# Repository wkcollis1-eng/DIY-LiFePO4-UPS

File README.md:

<div align="center">

# DIY LiFePO₄ UPS for a Home Assistant Host & Xfinity XB7 Modem

**12 V LiFePO₄ DC UPS · 18 V boost rail for the host · ESPHome coulomb-counting monitor · bench top-off charger (commissioning)**

</div>

A 12 V LiFePO₄ DC uninterruptible power supply. It keeps a Home Assistant host (ASRock N100DC-ITX) and an Xfinity XB7 cable modem running through grid outages, shuts the host down cleanly before the battery runs out, and recovers by itself when power returns. A Mean Well DIN-rail supply floats a 10 Ah pack through a MOSFET ideal diode. A Victron BatteryProtect provides the hardware low-voltage disconnect. An 18 V Pololu boost feeds the host. An ESPHome monitor on a purpose-built carrier PCB coulomb-counts every outage into Home Assistant.

The project was built in early 2026 around a Home Assistant Green, which ran directly on the 12 V bus. That host has been retired. The HA host is now the N100DC, which has run from this UPS since 2026-08-29; its 19 V ±10 % input window [S, ASRock N100DC-ITX manual] is why the boost exists. Documents dated before August 2026 describe the HA Green build; [Documentation](#documentation) says which ones are current.

Figures in this README carry the repository's provenance tags: **[M]** measured, **[S]** specification or prior document, **[D]** derived from [M]/[S] by stated arithmetic, **[I]** inferred and not yet tested, with the observation that would falsify it.

> **Honest context:** An $85 APC BE600M1 provides comparable backup for a modem and a small host. The case for building this instead (no inverter stage, sub-millisecond DC switchover by design, LiFePO₄ chemistry, direct Home Assistant telemetry) is in [design-rationale.md](docs/design-rationale.md). That document and its 10-year cost comparison were written for the March 2026 HA Green build and do not include the boost or the monitor PCB. Build this if those tradeoffs matter to you, and read [Current status](#current-status) first.

---

## ⚠️ Safety Warning

> [!CAUTION]
> **This project involves lithium batteries and AC mains voltage.** Improper handling can cause fire, electric shock, or equipment damage.

- ✅ **Disconnect AC power** before any work inside the enclosure
- ✅ Use appropriate **fusing** on battery connections
- ✅ Never charge LiFePO4 below **0°C (32°F)**
- ✅ Keep a **Class B or ABC fire extinguisher** accessible
- ✅ Follow the boost's energization order, OP-1 in [boost-subsystem-design.md](UPS-Monitor/boost-subsystem-design.md): *battery last-off, first-on; host barrel jack last-on, first-off*. This keeps the host off every connect transient.
- ✅ Review [docs/safety.md](docs/safety.md) before building

**Disclaimer:** Information provided for educational purposes only. Build at your own risk.

---

## Current Status

*As of 2026-10-16.*

| Area | State |
| :--- | :--- |
| Service | In service. Carries the XB7, and since 2026-08-29 the N100DC host |
| Protection ladder | Run end-to-end to the hardware LVD for the first time on 2026-09-15, including survival sleep; recovered with no intervention [M] |
| Capacity | **Well below its May 2026 value, by more than the test conditions can explain; cause not yet identified** (below) |
| Unattended recovery | Guaranteed only for outages that reach LVD, until the boost EN shed is fitted (below) |
| Monitor | UPS-Monitor-THT Rev 1 PCB, ESPHome firmware V1.20 (deployed 2026-09-16) |
| Top-off charger | Built and on the bench, design rev 0.17. Firmware V0.5 flashed 2026-10-30; 17 sessions so far, five of them DONE and the last ten on the UPS's own pack, and one BMS cut missed by FW-5 on V0.4, whose fix in V0.5 stays open until T17 (O18). T0–T17 not yet run |

> [!IMPORTANT]
> **Capacity shortfall.** On 2026-09-15 the pack delivered **2.5331 Ah / 31.821 Wh** from onset to LVD [M, firmware coulomb counter; independent HA-side integration agrees to +0.95 %]. Over the same voltage span at the same load, it delivered **42.4 % less charge than on 2026-09-01**, fourteen days earlier [D, [09-15 report](reports/UPS_Report_2026-09-15_Full_Discharge_Survival_Test.md) §4.3, n = 1 run each]. Measured LVD to LVD, it is 39.4 % below the 4.179 Ah of 2026-05-06 [D, same report]. Rate effects, Peukert, float droop and temperature together account for under 10 % of the LVD-to-LVD gap and none of the load-matched gap [D, §4.4].
>
> The leading candidate is cell imbalance or one weak cell [I, §4.5]. The direct falsifier, per-cell voltage at the end of discharge, cannot be measured: the pack is sealed and has no balance taps. Open Items 14a and 16 are the non-invasive substitutes ([Open work](#open-work)).
>
> **Every runtime and capacity figure from before September 2026, including the "~3.6 h / 4.18 Ah" this README used to quote, describes a pack and a load that no longer exist.**

### Unattended-recovery gap

The boost takes its input from the BP-65 load output, and its EN pin is not yet driven. `hassio.host_shutdown` therefore leaves the N100DC in S5 soft-off with 18 V still applied. Its BIOS setting *Restore on AC/Power Loss = Power On* acts only on a power cycle at the jack. **If AC returns after the graceful shutdown but before the pack reaches LVD, the host stays off until someone presses its power button** [D, [08-31 report](reports/UPS_Report_2026-08-31_Boost_Integration.md) §3].

Outages that reach LVD do recover, because the BP-65 collapses the rail. On 2026-09-15 the host booted with no button press after AC was restored [M]. The 09-15 report's Open Item 1 records why one operator-timed restoration does not fully establish the BIOS behaviour.

The fix is designed and not built: an EN shed from the monitor through an N-FET, latched low for the rest of the outage and released only on confirmed AC return. In [BOOST-DS-r1](UPS-Monitor/boost-subsystem-design.md) this is design rule DR-1 and procedure OP-2.

---

## System Overview

```
 120 VAC ─► Mean Well HDR-60-12 ─► MOSFET ideal diode ─┐
            13.3 V float, 54 W / 4.5 A                 │
                                                       ▼
            ┌──────────────────────── 12 V bus (Wago) ──────────────────────┐
            │                                                               │
     INA260 (battery branch, + = charging)                       Victron BP-65 LVD
            │                                               off 11.80 V / on 12.80 V + 30 s
   Cyclenbatt 12 V 10 Ah LiFePO₄                                            │
   (sealed, internal BMS)                                ┌──────────────────┴─────────────────┐
            │                                            ▼                                    ▼
   UPS-Monitor-THT  ◄── TB1 → F1 1 A                Xfinity XB7                    Pololu U3V70A boost
   XIAO ESP32-C3 · D24V7F3 · DS18B20                (12 V direct)                  18.0 V · 5 A-fused lead
            │ Wi-Fi                                                                           ▼
            └──────────────────────────► Home Assistant ◄──────────────────── ASRock N100DC-ITX (HA host)
```

When AC is present, the PSU holds the bus at float and the pack sits at equilibrium. When AC fails, the ideal diode blocks and the pack carries the loads. The monitor is fed upstream of the BP-65, so it stays powered after the LVD trip and can run survival sleep. It measures the battery branch: the INA260 sits between the Wago bus (VIN+) and Battery+ (VIN−), and the metered current runs on 16 AWG through the breakout's own terminals, not through PCB copper [S, `ups-monitor.yaml` header].

---

## Key Specifications

| Parameter | Value | Basis |
| :--- | :--- | :--- |
| PSU | Mean Well HDR-60-12, 54 W / 4.5 A, trimmed to 13.3 V and lacquered | [S, HDR-60 datasheet] |
| Float at the bus, boost era | 13.1970 V mean (13.2325 V before the boost), 23.3 mV above the 13.15 V on-battery threshold; 0 false on-battery events in 26,413 samples | [M, 08-31 report] |
| Battery | Cyclenbatt 12 V 10 Ah LiFePO₄, 4S, sealed: no balance taps, no BMS telemetry | [S, nameplate]; sealed [M, owner] |
| Usable capacity | **2.5331 Ah / 31.821 Wh**, onset to LVD, 2026-09-15. Under investigation | [M] |
| LVD | Victron BP-65: disconnect 11.80 V after its delay, reconnect 12.80 V after 30 s. Trips seen: 11.77 V (2026-03-26); last telemetry before the 2026-09-15 trip 11.675 V | [S, BP-65 manual]; trips [M] |
| Load on battery | 2.089 A / 26.80 W steady, 2.533 A / 32.48 W peak (host + XB7 + monitor) | [M, 2026-08-29 outage, n = 156] |
| Load after host shutdown | ~1.40 A (XB7 + monitor) | [M, 2026-09-15] |
| AC at the outlet | 30.554 W with the boost; 16.832 W before it | [M, 08-31 report] |
| Boost | Pololu U3V70A set to 18.0 V and lacquered; input from the BP-65 load output; EN not yet driven | [S, BOOST-DS-r1] |
| Host input window | 17.1–20.9 V (19 V ±10 %) | [S, ASRock N100DC-ITX manual] |
| Recharge | Limited by the PSU's 4.5 A constant-current limit: peak captured 4.4465 A, a lower bound | [S]; [M, 2026-09-15] |
| Switchover | No interruption seen by the XB7 or the host in the 2026-08-29, 09-01 or 09-15 outages. The <1 ms figure is the ideal diode's design value, not a measurement: 5 s telemetry cannot resolve it | [M]; <1 ms [S] |
| Monitor | UPS-Monitor-THT Rev 1: XIAO ESP32-C3, Adafruit INA260 (socketed), DS18B20, Pololu D24V7F3; ESPHome firmware V1.20 | — |
| Enclosure | LeMotech ABS, 9.6″ × 7.6″ × 4.5″; IP65 as sold, IP4X once vented | [S, [supplemental-analysis.md](docs/supplemental-analysis.md)] |
| Build cost | $223.88 for the March 2026 build; excludes the monitor PCB and the boost subsystem | [S, [bom.md](docs/bom.md)] |

---

## Operating Modes and Protection Ladder

Thresholds are the V1.20 firmware's substitutions [S, [`ups-monitor.yaml`](UPS-Monitor/ups-monitor.yaml)]. The Home Assistant side is the `ups_*_v3` automation chain in [home-assistant-config](https://github.com/wkcollis1-eng/home-assistant-config).

1. **AC present.** The PSU holds the bus at float through the ideal diode, and the pack sits at about 0 A. The 13.3 V ceiling keeps the bus inside what the loads tolerate, at the cost of holding the pack near 65 % SOC [S, 05-06 report §4.3]. That is why the [top-off charger](#planned-top-off-charger) is planned.
2. **AC fails.** The ideal diode blocks and the pack carries the loads with no interruption. `on_battery` sets when the bus falls below 13.15 V.
3. **Discharge phases.** The firmware tracks Settling, then Plateau (≥ 12.65 V), Knee (12.40–12.65 V) and Cliff (≤ 12.40 V). It counts Ah and Wh and estimates the runtime remaining.
4. **Graceful host shutdown.** Home Assistant calls `hassio.host_shutdown` on the first of three triggers, after a 30 s revalidation:
   - `cliff_imminent`: EMA voltage slope below −10 mV/min, with V < 12.65 V and the pack discharging, held 180 s;
   - `voltage_warning`: 12.40 V;
   - a runtime estimate under 8 min.

   The XB7 stays up.
5. **Hard fallback.** `voltage_critical` (12.20 V, held 10 s) calls the host shutdown with no revalidation, in case the graceful path has not completed.
6. **LVD.** The BP-65 opens at 11.80 V after its delay, dropping the XB7 and the boost. The monitor stays powered.
7. **Survival sleep.** When the load collapses at the trip (on battery, −0.30 A < I < +0.20 A), the monitor deep-sleeps in 120 s cycles with at most 60 s awake each, rather than draining the pack awake, and records each wake voltage in flash. It exits when V ≥ 13.0 V.
8. **AC returns.** The PSU recharges at its 4.5 A current limit and the BP-65 reconnects 30 s after the bus passes 12.80 V. The boost restarts, and the host powers on if it lost DC (see the [recovery gap](#unattended-recovery-gap)).

**What the record shows about the ladder:**

- **Graceful shutdown.** It first fired in May 2026, via `cliff_imminent`. In both boost-era runs, every attempt aborted at least once before one held [D, the firmware replayed on both runs' data, 09-15 report §6.1, n = 2; the 09-15 abort was also seen in HA, M]. The slope term's noise is sd 18.7–24.0 mV/min against a −10 mV/min threshold [M]. V1.20 raised the hold from 60 s to 180 s for this reason, and that change has not yet been exercised in an outage.
- **`voltage_critical` fallback.** It has never been the path that shut a running host down [M].
- **Host-down to LVD.** On 2026-09-15 this took 52 min 47 s at ~1.40 A, with the BP-65 as the only protection [M]. That margin was measured on a pack whose capacity is changing, so it does not set a threshold.

---

## Monitor

### Hardware: UPS-Monitor-THT Rev 1

- KiCad 10, 2-layer, 44 × 77 mm, drawn for OSH Park [S, `ups-monitor.yaml` header]. It replaced the SBB400 breadboard build.
- The Adafruit INA260 (#4226) breakout sits in socket U2. The metered current never touches PCB copper. The board's own supply runs from TB1 through F1 (1 A slow-blow) to a Pololu D24V7F3 3.3 V regulator.
- DS18B20 battery probe on TB2. I²C on GPIO6/GPIO7, 1-Wire on GPIO10.
- Files: [`UPS-Monitor-THT.kicad_pcb`](UPS-Monitor/UPS-Monitor-THT.kicad_pcb), Gerbers in [`UPS-Monitor-THT-Rev_1.zip`](UPS-Monitor/UPS-Monitor-THT-Rev_1.zip), and renders in [`UPS-Monitor/`](UPS-Monitor/).
- The U2 footprint also accepts an INA228 breakout. The firmware is INA260-specific, and an INA228 remaps socket pin 5, so do not substitute one without re-validating.

### Firmware: `ups-monitor.yaml` V1.20

[`UPS-Monitor/ups-monitor.yaml`](UPS-Monitor/ups-monitor.yaml) is the deployed build, byte-identical to the file on the HA host. Credentials resolve through `!secret`; no `secrets.yaml` is in this repository. Every revision is recorded in its header changelog.

What the firmware does:
- coulomb-counts Ah and Wh per outage and over the pack's life;
- runs the discharge-phase state machine and the `cliff_imminent` slope detector;
- estimates runtime remaining;
- estimates internal resistance at outage onset;
- keeps survival-sleep records in NVS;
- watches for stale INA260 data.

V1.20 (2026-09-16) changes:
- V, I and P are now published from one paired read. Before, they ran on free-running clocks, with a V-to-I skew re-drawn on every boot (~1.29 s on the 09-15 boot [M, 09-15 report §10.3]);
- a windowed Apparent-Ri gate;
- `cliff_imminent` hold raised from 60 s to 180 s;
- outage duration now stops at AC return;
- hysteresis on the fully-charged detector.

The survival-sleep design is documented in [`UPS_SurvivalSleep_Design_Summary_v12.md`](UPS-Monitor/UPS_SurvivalSleep_Design_Summary_v12.md). That document tracks the firmware through V1.14, and its currency note lists what changed after.

> [!NOTE]
> **Known issue: the `INA260 Alert` entity cannot fire.** The Rev 1 PCB routes the INA260's ALERT (socket pin 5, R2 pull-up) to XIAO D3 = GPIO5. The firmware, and its header pin map, read GPIO3 (D1), which is unconnected [M, KiCad pad positions; owner-confirmed 2026-10-01]. Nothing depends on it: the firmware arms no alert condition and no automation reads the entity. A one-pin fix is written and held until it can be bench-tested.

---

## Test History

| Date | Event | Load | Result | Source |
| :--- | :--- | :--- | :--- | :--- |
| 2026-03-25/26 | Commissioning: two discharges on a substitute load (Netgear R6400) | ~7 W DC | BP-65 tripped at 11.77 V [M, Shelly ADC] | [commissioning.md](docs/commissioning.md) |
| 2026-03-26 → 04-05 | Commissioning window and relocation to the permanent site | HA Green + XB7 | Stable float | [04-05 report](reports/UPS_Report_2026-04-05.md) |
| 2026-05-06 | Outage to LVD; first INA260 coulomb count; first graceful shutdown | HA Green + XB7, 1.18 A / 14.9 W | **4.179 Ah / 53.271 Wh** [M]; ~213 min AC-fail to LVD [D, 10:25:20 → ~13:58:30 UTC] | [05-06 report](reports/UPS_Report_2026-05-06.md) |
| 2026-06-18 | Partial outage; AC restored at 12.452 V, before any cliff | 1.186 A / 15.18 W | 3.62 Ah / 46.34 Wh in 183.3 min [M]; no protection automation fired | [06-18 report](reports/UPS_Report_2026-06-18.md) |
| 2026-08-29 | First outage after the boost was fitted | 2.089 A / 26.80 W | XB7 and host held through switchover [M] | [08-31 report](reports/UPS_Report_2026-08-31_Boost_Integration.md) |
| 2026-09-01 | Deliberate test, stopped at 12.565 V | host + XB7 | 1.833 Ah / 23.369 Wh in 54 min [M] | [08-31 report](reports/UPS_Report_2026-08-31_Boost_Integration.md) |
| 2026-09-15 | **Full discharge to LVD; first survival sleep; recharge** (firmware 1.19) | ~2.05 A, falling to ~1.40 A after the host shut down | **2.5331 Ah / 31.821 Wh** in 1 h 30 m 08 s onset to LVD [M] | [09-15 report](reports/UPS_Report_2026-09-15_Full_Discharge_Survival_Test.md), [data](data/2026-09-15_full_discharge_survival_test/README.md) |

All runs are on the same pack. May and June were on the pre-boost load (~1.18 A); August onward on the N100DC load. None of the pre-September figures predicts the present pack.

### 2026-09-15: what it established

- **Full ladder to the hardware LVD.** The run went Plateau → Knee (09:41:48) → Cliff (10:32:50) → BP-65 trip (10:47:18). The cliff lasted 14 min 28 s [M].
- **Survival sleep, first real exercise.** It ran 5 sleep/wake cycles over a ~12 min 51 s blackout. Wake voltage rose from 11.9275 to 11.9762 V, consistent with an unloaded pack relaxing. It exited cleanly, and the system recovered unattended [M].
- **The recharge is PSU-limited, not pack-limited.** The captured peak, 4.4465 A, is 98.8 % of the HDR-60-12's 4.5 A rating [D, 4.4465 ÷ 4.5]. The bus re-crossed 13.15 V 39 min 25 s after charge current was first seen [D, 11:00:13.67 → 11:39:39]. At the report cutoff, 51 min 49 s in [D, 11:00:13.67 → 11:52:03], 0.792 A was still flowing [M]. A recharge to termination has not been observed (Open Item 16).
- **Data caveats.** The InfluxDB export covers 37.5 of the ~90 discharge minutes, and it holds one stale sample per series written on recorder restart. Read the [reproduction guide](data/2026-09-15_full_discharge_survival_test/README.md) before re-analysing.

### Commissioning, March 2026

The March 25–26 commissioning ran two full discharges on a Netgear R6400 substitute load (~7 W DC), logged by the Shelly Plus Uni at 5 s intervals. The BP-65 tripped at **11.77 V** against its 11.80 V setting [M], and the pack recovered to float on AC return. The Shelly was replaced by the INA260 monitor in April 2026. Its voltage-profile capacity estimate (D3: 4.85 Ah / 62.5 Wh) was superseded by the May coulomb count and should not be used as a baseline.

---

## Open Work

In priority order, from the [09-15 report](reports/UPS_Report_2026-09-15_Full_Discharge_Survival_Test.md) §11 and the [08-31 report](reports/UPS_Report_2026-08-31_Boost_Integration.md) §7:

1. **Open Item 14a: repeat the full discharge at May's current.** Shut the host down before cutting AC, so the load is the XB7 and the monitor only (~1.2–1.4 A). Use the same 11.80 V endpoint and the same instrument as 2026-05-06. This is the decisive capacity test, and it is also the first outage to exercise V1.20's 180 s `cliff_imminent` hold.
2. **Open Item 16: coulomb-count one recharge to termination**, then compare it with the discharge count. This separates real fade from incomplete charge.
3. **Boost EN shed** (DR-1/OP-2) to close the [recovery gap](#unattended-recovery-gap), and the BOOST-DS-r1 §10 scope gate (V1–V5), which is still open.
4. **Build the top-off charger**, then run 14a before and after a top-balance hold.
5. **Fix the INA260 ALERT pin** once it can be bench-tested.

---

## Planned: Top-Off Charger

[`Top-Off-Charger/top-off-charger-design.md`](Top-Off-Charger/top-off-charger-design.md) is the design, rev 0.17, dated 2026-11-02. The board is built, with one rework (its #2814 control pin, design §7.2). §11.1 records the first bench sessions, and §11.2 the first on the UPS's own pack.

The 13.3 V float never takes the cells to balancing voltage. The plan is to take the pack out of the UPS for each session, charge it to full on a Dylannet P20 at 5 A, and then hold it at 14.40 V on a Mean Well HDR-30-15 (worst case ≤ 3.64 A [D, design §4.1]). An ESPHome controller times the hold and logs the current tail.

- **Controller board.** Top Off Charger PCB rev 0.8: KiCad 10, 2-layer, 29.5 × 78 mm, for OSH Park. It carries a XIAO ESP32-C3, an Adafruit INA228 (#5832) with a 15 mΩ shunt, a Pololu #2814 MOSFET switch, a Pololu #5382 ideal diode, a D24V7F3 regulator, a status LED and a Kelvin ground for the INA228. DRC: 0 errors / 34 warnings / 0 unconnected [M]. **Built** (2026-10-28; which file went to fab is not recorded, O11).
- **Protection.** A protection ladder (L1–L8), firmware requirements (FW-1–FW-14) and acceptance tests (T0–T17). The design requires each session to end by itself within its time cap, and nothing to restart a charge after a reboot or an AC blip. Stop, the normal DONE and FW-5 have now worked on the bench, and FW-5 has also missed once (O18); the numbered tests have not run.
- **Firmware.** [`firmware/top-off-charger.yaml`](Top-Off-Charger/firmware/top-off-charger.yaml) V0.5 compiles, was replayed against the five sessions V0.4 ran, and has been flashed since 2026-10-30; it has run two more. T0–T17 have not run (O4, O18).
- **What it cannot do.** It cannot balance a pack whose BMS has no balancer, and nothing documents whether this one has one. The current tail at 14.40 V is the first direct look [I; falsifier: the logged current decays toward zero with no floor]. On 2026-10-29, on a second, new Cyclenbatt pack rather than the UPS's, it fell to 0.16–0.34 mA at 14.30–14.40 V, with no balancer-sized floor [M, design §11.1], and to about 0.13 mA net after 8 h near 14.45 V on 2026-10-30 [D, design §11.1]. The success measure is Open Item 14a before and after. It does not serve Open Item 16, because the P20 does the bulk charge outside its INA228 and has no data port, so its Ah is a hand reading off its display (O10).

---

## Assembly

*Elevation (top) and plan (bottom) views of the LeMotech junction box, interior dimensions in inches. This drawing and the block diagram below predate the boost and the THT monitor PCB.*

---

## Documentation

**Current**

| File | Contents |
| :--- | :--- |
| [reports/UPS_Report_2026-09-15_Full_Discharge_Survival_Test.md](reports/UPS_Report_2026-09-15_Full_Discharge_Survival_Test.md) | Full discharge to LVD, first survival sleep, recharge, capacity shortfall (r3) |
| [data/2026-09-15_full_discharge_survival_test/](data/2026-09-15_full_discharge_survival_test/README.md) | Raw series, logs, capture scripts and reproduction guide for that report |
| [reports/UPS_Report_2026-08-31_Boost_Integration.md](reports/UPS_Report_2026-08-31_Boost_Integration.md) | Boost integration: float and trip-margin effects, outage load, unattended-recovery gap |
| [boost-subsystem-design.md](UPS-Monitor/boost-subsystem-design.md) | BOOST-DS-r1: 18 V boost design, failure analysis, rules DR-1 and OP-1–OP-4, scope gate |
| [UPS-Monitor/ups-monitor.yaml](UPS-Monitor/ups-monitor.yaml) | Monitor firmware V1.20 (header holds the pin map and full changelog) |
| [UPS-Monitor/UPS_SurvivalSleep_Design_Summary_v12.md](UPS-Monitor/UPS_SurvivalSleep_Design_Summary_v12.md) | Survival-sleep engineering basis (tracks firmware through V1.14) |
| [HA Automation/README_HA_UPS_Integration.md](HA%20Automation/README_HA_UPS_Integration.md) | Home Assistant side: the entities, the five `ups_*_v3` automations and their guards, and what the test record shows about them |
| [Top-Off-Charger/top-off-charger-design.md](Top-Off-Charger/top-off-charger-design.md) | Top-off charger design, rev 0.13 (built; commissioning) |
| [CHANGELOG.md](CHANGELOG.md) | Repository changelog |

**Earlier reports** (pre-boost load; figures predate the boost and the September capacity result)

| File | Contents |
| :--- | :--- |
| [reports/UPS_Report_2026-06-18.md](reports/UPS_Report_2026-06-18.md) | Partial outage; decomposition of its charge delta against May |
| [reports/UPS_Report_2026-05-06.md](reports/UPS_Report_2026-05-06.md) | Outage to LVD; first INA260 coulomb count; graceful shutdown confirmed |
| [reports/UPS_Report_2026-04-05.md](reports/UPS_Report_2026-04-05.md) | Inaugural commissioning report |

**Original design set, January–May 2026** (the HA Green build. Figures for load, runtime, cost and lifespan predate the boost and the September capacity result)

| File | Contents |
| :--- | :--- |
| [docs/bom.md](docs/bom.md) | Bill of materials with vendor, price, and notes |
| [docs/wiring.md](docs/wiring.md) | From/to wiring tables, fuse locations, component mounting |
| [docs/specifications.md](docs/specifications.md) | Electrical, performance, and protection spec tables |
| [docs/design-rationale.md](docs/design-rationale.md) | Build-vs-buy analysis, float charging strategy |
| [docs/component-selection.md](docs/component-selection.md) | Per-component selection rationale |
| [docs/cost-analysis.md](docs/cost-analysis.md) | Build cost and 10-year lifecycle comparison |
| [docs/safety.md](docs/safety.md) | AC and battery safety procedures |
| [docs/voltage-drop-analysis.md](docs/voltage-drop-analysis.md) | Wiring resistance and voltage drop |
| [docs/supplemental-analysis.md](docs/supplemental-analysis.md) | Thermal budget, runtime analysis, FMEA |
| [docs/design-specification.md](docs/design-specification.md) | Requirements, design decisions, verification matrix |
| [docs/commissioning.md](docs/commissioning.md) | Commissioning process and results |
| [docs/UPS_Final_Report.pdf](docs/UPS_Final_Report.pdf) | One-page chart of the March 25–26 commissioning cycle on the R6400 substitute load: two discharges, the recharge between them, the LVD trip |
| [docs/ups_full_discharge_cycle_r6400.html](docs/ups_full_discharge_cycle_r6400.html) | The same R6400 cycle as an HTML chart |
| [docs/Final_As_Built_Performance_&_Cost_Summary.md](docs/Final_As_Built_Performance_&_Cost_Summary.md) | As-built performance and cost summary (HA Green build) |
| [docs/UPS_Validation_Report.md](docs/UPS_Validation_Report.md) | Validation report with Home Assistant configuration |

## Datasheets

- [Mean Well HDR-60-12 — Datasheet](https://www.meanwell.com/Upload/PDF/HDR-60/HDR-60-SPEC.PDF)
- [Victron Smart BatteryProtect BP-65 — Datasheet](https://www.victronenergy.com/upload/documents/Datasheet-Smart-Battery-Protect-65-A--100-A--220-A-EN.pdf)
- [Victron Smart BatteryProtect — Manual](https://www.victronenergy.com/upload/documents/Smart_BatteryProtect_12V_24V/114439-Smart_BatteryProtect-pdf-en.pdf)
- [Adafruit INA260 — Guide](https://learn.adafruit.com/adafruit-ina260-current-voltage-power-sensor-breakout) · [local PDF](UPS-Monitor/adafruit-ina260-current-voltage-power-sensor-breakout.pdf)
- [TI INA260 — Datasheet](https://www.ti.com/product/INA260)
- [Seeed Studio XIAO ESP32-C3 — Getting Started](https://wiki.seeedstudio.com/XIAO_ESP32C3_Getting_Started/) · [ESP32-C3 datasheet (local)](UPS-Monitor/esp32-c3_datasheet.pdf)
- [Pololu D24V7F3 — Datasheet (local)](UPS-Monitor/pololu_D24V7F3_datasheet.pdf)

---

## Related Projects

- [LiFePO₄ Battery Bank Study](https://github.com/wkcollis1-eng/Lifepo4-Battery-Banks): 500 Ah DIY battery bank with 130+ days of monitoring
- [Home Assistant Config](https://github.com/wkcollis1-eng/home-assistant-config): the live Home Assistant configuration, including this UPS's `ups_*_v3` automations

---

## Status

- [x] Design, build and commissioning (HA Green era, January–May 2026)
- [x] ESPHome INA260 monitor deployed (April 2026); moved to the UPS-Monitor-THT Rev 1 PCB
- [x] First coulomb-counted capacity and first graceful shutdown (2026-05-06)
- [x] N100DC host on the 18 V boost (2026-08-29)
- [x] Full discharge to hardware LVD and first survival sleep, recovered unattended (2026-09-15)
- [x] Firmware V1.20 deployed (2026-09-16)
- [ ] Capacity shortfall characterised (Open Items 14a, 16)
- [ ] Boost EN shed fitted, closing the unattended-recovery gap
- [ ] BOOST-DS-r1 §10 scope gate
- [ ] Top-off charger built and validated
- [ ] INA260 ALERT pin fix

---

## Notes

- The XB7 runs directly off the 12 V bus, with no DC-DC stage. Only the host has one, because its 17.1–20.9 V window [S] excludes the bus. Comcast publishes no DC input range for the XB7. The ±10 % tolerance assumed in `docs/` comes from IEC 62368-1 design practice, not from a specification [I; falsifier: a Comcast or adapter document giving a narrower range].
- The HA Green this UPS was designed around has left the bus, so the HA Green figures in `docs/` describe a configuration that no longer runs.

---

## 💝 Support This Project

If this build log or the design rationale saved you time or money on your own UPS project, consider sponsoring continued measurement and documentation work.

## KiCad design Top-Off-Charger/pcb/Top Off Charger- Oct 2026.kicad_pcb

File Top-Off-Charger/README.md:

# Does the BMS in a sealed LiFePO4 battery actually balance?

**A small, very cautious charger that holds a 12 V LiFePO4 pack at 14.40 V and logs every milliamp, to find out.**

> **Status (2026-10-31):** built and on the bench. Seven test sessions so far, on one spare pack. The real verdict, a before-and-after capacity test on the UPS's own pack, hasn't been run yet. This page will be updated as results come in.

---

## The question

My [DIY LiFePO4 UPS](../README.md) runs on a sealed 12 V, 10 Ah "drop-in" LiFePO4 battery. The UPS keeps it floating at 13.3 V, which is easy on the battery but never brings the cells up high enough for any balancing to happen.

Between two full discharge tests, the usable capacity the UPS got out of that pack fell from **4.18 Ah to 2.53 Ah** (one test each, measured from full down to the UPS's low-voltage cutoff). The way the voltage sagged suggested the four cells inside are no longer evenly matched.

The usual forum advice is: *every so often, charge it to 14.4–14.6 V and let it sit there, so the BMS can balance the cells.*

The trouble is that this pack is sealed. There are no balance leads, and the label says nothing about balancing. **So does it have a balancer at all?** You can't open it to look, but you can watch it. A balancer works by bleeding a little current off the fullest cell. If I hold the pack at a steady voltage, that bleed should show up as a current that tapers off but never reaches zero. No floor means no balancer, or at least none that's doing anything.

That needs a charger that can hold a voltage for hours, measure fractions of a milliamp, and be trusted to run with nobody watching.

## What it is

- **Mean Well HDR-30-15** DIN-rail supply, trimmed to about 14.4 V. It's a 2 A supply on purpose: even when it's overloaded, it physically can't push more than about 3.6 A, which is under the pack's 5 A charge limit.
- **Pololu MOSFET switch** to turn the charge on and off, and a **Pololu ideal diode** so the battery can never feed back into the supply.
- **Adafruit INA228** current and voltage monitor on a 15 mΩ shunt. It resolves about 20 µA per step, which is fine enough to see a balancer's bleed.
- **Seeed XIAO ESP32-C3** running ESPHome, reporting to Home Assistant once a second.
- A small two-layer carrier board (the purple one, from OSH Park) that ties it all together.

The pack gets its bulk charge on an ordinary hobby charger first. This box only does the long, slow hold at the top.

## Designed for when nobody's watching

The design starts from one question: *what if something fails while I'm not home?* Wi-Fi drops, Home Assistant crashes, the ESP32 hangs, or the supply's voltage drifts high. Every layer below answers one of those failures:

1. The firmware ends the session after a fixed time at voltage.
2. Hard firmware stops for over-voltage, over-current, a sensor dropping out, or the BMS cutting out.
3. If the ESP32 hangs or reboots, the switch falls **off** by itself through its own pull-down resistor.
4. After a power blip or reboot, nothing ever restarts a charge on its own.
5. A plain mechanical countdown timer on the AC plug, with no network, ends everything regardless.
6. The battery's own BMS.
7. A 5 A fuse right at the battery's + terminal, so a short anywhere in the lead or the box is fused at the source.

No alligator clips. The lead ends in insulated quick-disconnects, and polarity is checked before every connection.

## What I've found so far

Seven sessions on a new spare pack of the same model, not the UPS's pack yet:

- **The BMS cut out at 14.31 V**, three times in one evening, with about 1 A flowing. That's well under the 14.6 V on the label. My best guess, not yet proven, is that one cell reaches its limit before the others.
- **At 14.40 V, the current tapered all the way down to about 0.2 mA** over six hours. A typical passive balancer bleeds tens of milliamps. Whatever this pack has, it's bleeding **less than about a third of a milliamp**. At that rate, evening out a 0.25 Ah mismatch would take more than 700 hours, about a month of continuous holding.
- **At 14.50 V, the BMS cut out after 98 seconds** with only 11 mA flowing. The cell that tripped was still charging when it cut, so no meaningful bleed was running on it.
- **An 8-hour hold at about 14.45 V** tapered to around 0.13 mA, with a dozen brief BMS dropouts along the way.

**Where that leaves things:** if this pack has a balancer, I can't see it doing anything at the voltages the label allows. That comes from one pack and short tests. A balancer that only runs at higher charge currents would be invisible to this method. The test that actually settles it is coming next: top off the UPS's own pack, then repeat the full discharge test and see whether the lost capacity comes back.

## Things that bit me

- **The control trace went to the wrong pin.** The board routes the ESP32's output to the Pololu switch's SW pin instead of its ON pin. A bodge wire fixed it, and the next board revision moves the trace.
- **The INA228 breakout's VBUS jumper was open**, so voltage readings came from an unconnected pin until I closed it. Now it's a build step.
- **Saving the board without refilling the ground pour shorted a power net to ground** in the saved file. KiCad's design-rule check on the saved file caught it before anything was ordered.
- **Plugging the battery in with AC on reset the ESP32** every time. Each time it came back with the switch safely off, which is what the design promised, but it's still not how it's meant to be connected.

## About the design doc

[`top-off-charger-design.md`](top-off-charger-design.md) is long. Every number in it is tagged as measured, from a spec sheet, calculated, or inferred. I wrote it with Claude Code as a drafting partner, and it keeps "correction records" for the places where the reasoning went wrong and got caught. Two of those changed the hardware. One moved the bulk charging off this supply, after the datasheet showed that running it in overload is a fault condition, not a charging mode. The other kept the cheaper Pololu switch, after a misread temperature rating was caught.

## Files

| Folder | What's in it |
|---|---|
| [`top-off-charger-design.md`](top-off-charger-design.md) | Full design, test plan, and bench results |
| [`firmware/`](firmware/) | ESPHome YAML for the XIAO ESP32-C3 |
| [`pcb/`](pcb/) | KiCad board file (2-layer, 29.5 × 78 mm) |
| [`assests/`](assests/) | Photos |

Part of the [DIY-LiFePO4-UPS](../README.md) project. Licensed under the repository's [LICENSE](../LICENSE).

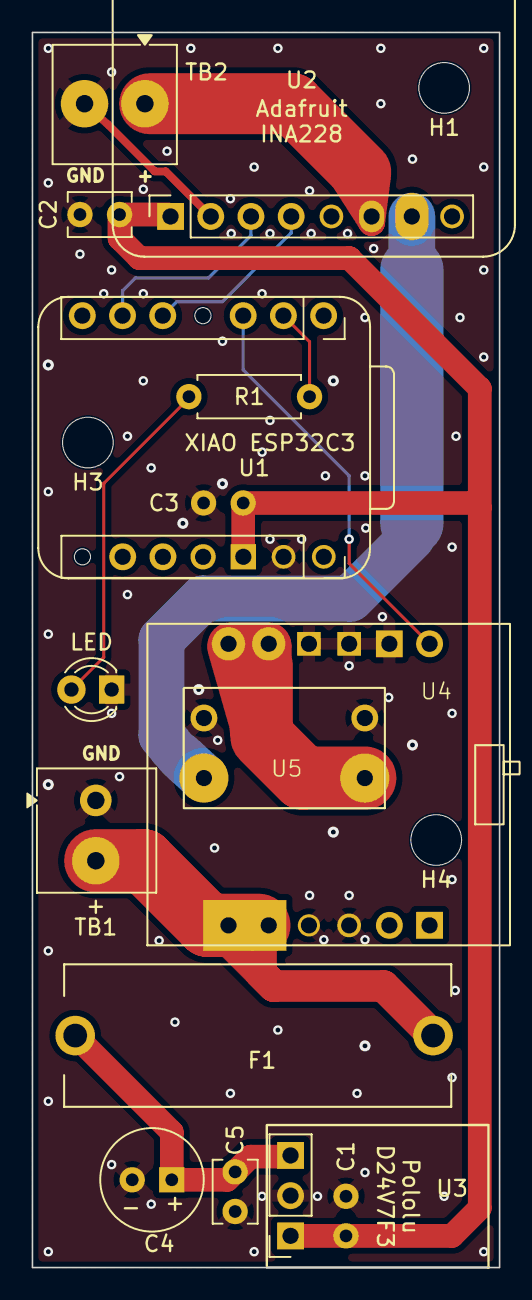
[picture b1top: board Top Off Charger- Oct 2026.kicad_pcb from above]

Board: 2 copper layers, 29.5 x 78.0 mm, 19 parts (0 on the bottom side), 13 nets.

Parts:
C1: CAP CER 10UF 10% 25V X7R RADIAL, FG18X5R1E106MRT00; C_Disc_D5.0mm_W2.5mm_P2.50mm
C2, C3, C5: CAP CER 0.1UF 50V X7R RADIAL, K104K10X7RF53L2; C_Disc_D3.8mm_W2.6mm_P2.50mm
C4: CAP ALUM 47UF 20% 50V RADIAL TH, EEU-FR1H470; C_Radial_D6.3mm_H11.0mm_P2.50mm
F1: FUSEHOLDER BLOCKS - PCB - CLIP C, 696108003002; Wuerth_696108003002
H1, H3, H4: M3; MountingHole_3.2mm_M3
LED: LED GREEN DIFFUSED T/H LED_D5.0mm - LTL-4231N; LED_D3.0mm
NT1: NetTie-2_SMD_Pad0.5mm
R1: 1 kOhms ±5% 0.25W, 1/4W Through Hole Resistor Axi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; R_Axial_DIN0207_L6.3mm_D2.5mm_P7.62mm_Horizontal
TB1, TB2: TERM BLK 2P SIDE ENT 3.81MM PCB, 5442756; TerminalBlock_Phoenix_MKDS-1-2-3.81_1x02_P3.81mm_Horizontal
U1: Xiao ESP32C3; XIAO ESP32C3
U2: Adafruit INA228 5832; Adafruit INA228
U3: Pololu D24V7F3; PinSocket_1x03_P2.54mm_Vertical
U4: Big MOSFET Slide Switch with Reverse Voltage Prot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; Pololu Mosfet Switch
U5: Pololu Ideal Diode Reverse Voltage Protector, 4-6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; Pololu Ideal Diode 5382

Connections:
+3V3: C1.1, C2.2, C3.2, U1.3V3, U2.1, U3.1
BATT_RAW: F1.1, TB1.2, U4.11, U4.12
Batt_SW: U4.5, U4.6, U5.1
GND: C1.2, C2.1, C3.1, C4.2, C5.1, LED.1, NT1.1, TB1.1, TB2.2, U1.GND, U3.2, U4.2, U4.3, U4.4, U4.9, U4.10, U5.2, U5.4
GND_SENSE: NT1.2, U2.2
GPIO3: R1.1, U1.D1
GPIO3_LED: LED.2, R1.2
GPIO4_SW: U1.D2, U4.1
SCL: U1.SCL, U2.3
SDA: U1.SDA, U2.4
VIN+: U2.7, U5.3
VIN-: TB2.1, U2.6
V_Fused: C4.1, C5.2, F1.2, U3.3

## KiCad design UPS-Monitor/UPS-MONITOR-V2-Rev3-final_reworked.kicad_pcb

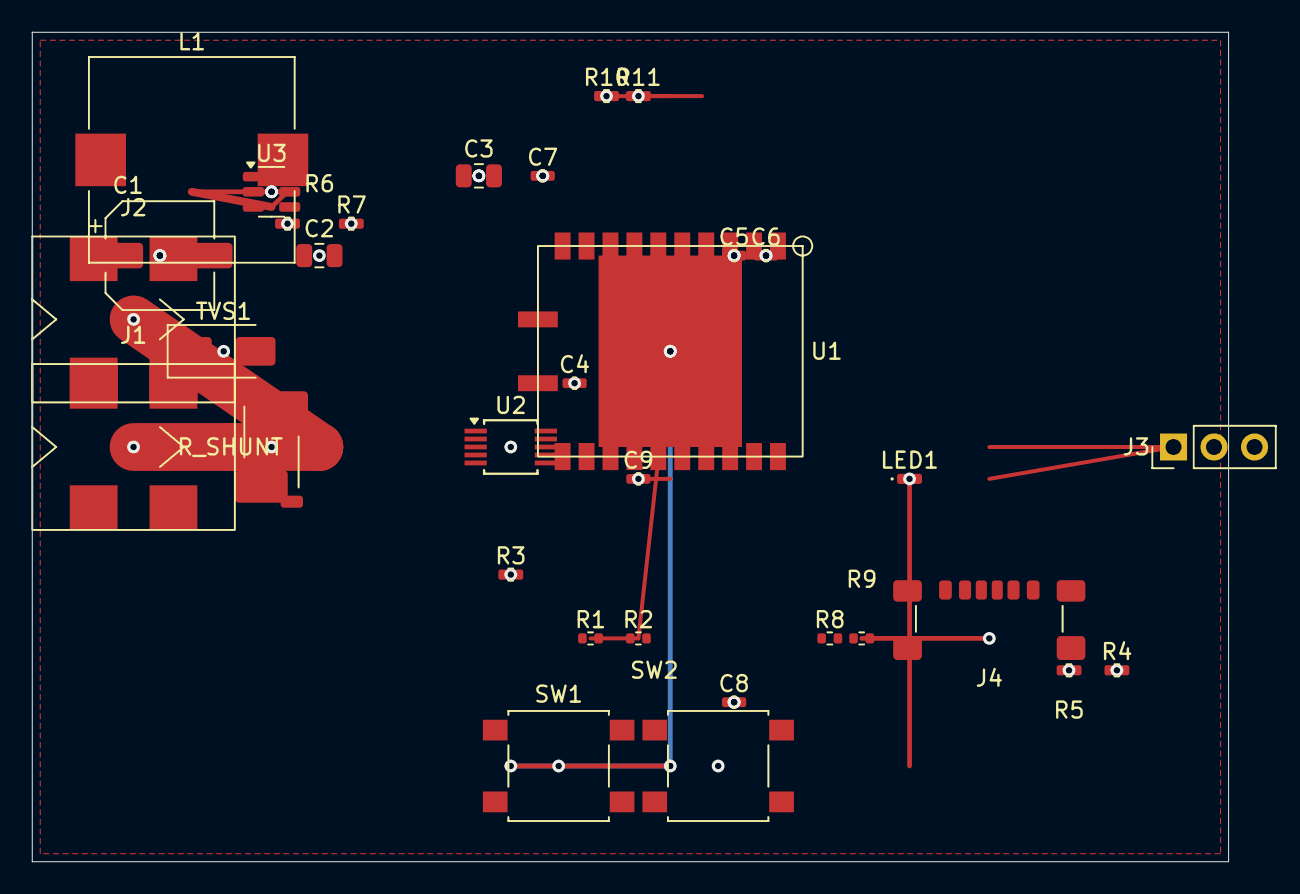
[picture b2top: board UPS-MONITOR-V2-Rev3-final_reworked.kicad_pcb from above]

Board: 4 copper layers, 75.0 x 52.0 mm, 33 parts (0 on the bottom side), 19 nets.

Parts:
C1: 100uF 25V; C1
C2: 10uF 25V; C2
C3: 22uF 10V; C3
C4: 100nF; C4
C5: 100nF; C5
C6: 100nF; C6
C7: 100nF; C7
C8: 1uF; C8
C9: 100nF; C9
J1: BATT_IN; J1
J2: LOAD_OUT; J2
J3: PinHeader 1x03; J3
J4: USB4135-GF-A; J4
L1: 4.7uH IHLP-5050; L1
LED1: Blue 0402; LED1
R1: 4.7k; R1
R2: 4.7k; R2
R3: 10k; R3
R4: 100R; R4
R5: 10R; R5
R6: 210k; R6
R7: 68k; R7
R8: 10k; R8
R9: 4.7k; R9
R10: 5.1k; R10
R11: 5.1k; R11
R_SHUNT: WSLT2512R0100FEA; R_SHUNT
SW1: B3S-1000; SW1
SW2: B3S-1000; SW2
TVS1: SMAJ15CA; TVS1
U1: ESP32-C3-MINI-1-N4; U1
U2: INA228AIDGST; U2
U3: AP63203WU-7; U3

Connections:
+3V3: C3.1, C4.1, C5.1, C6.1, C7.1, J3.1, L1.2, LED1.2, R1.1, R2.1, R4.1, R6.1, R8.1, R9.1, U1.2, U2.10
BATT_IN: J1.1, R_SHUNT.1, TVS1.2
BOOT_N: SW1.1, U1.13
DS18B20: J3.2, R9.2, U1.4
EN_RC: C8.1, R8.2, SW2.1, U1.16
FB_BUCK: R6.2, R7.1, U3.3
GND: C1.1, C2.2, C3.2, C4.2, C5.2, C6.2, C7.2, C8.2, C9.2, J1.2, J2.2, J3.3, J4.S1, R3.1, R3.2, R7.2, R10.2, R11.2, SW1.2, SW2.2, TVS1.1, U1.1, U1.3, U1.6, U1.7, U1.9, U1.10, U1.11, U1.17, U1.18, U1.19, U1.20, U1.21, U1.22, U1.GND, U2.1, U2.4, U2.5, U2.6, U3.2
LED_K: LED1.1, R4.2, U1.5
LOAD_OUT: C1.2, C2.1, J2.1, J4.A9, J4.B9, R5.1, R_SHUNT.4, U3.4, U3.5, U3.6
SCL: R2.2, U1.12, U2.7
SDA: R1.2, U1.8, U2.8
SHUNT_HI: R_SHUNT.2, U2.3
SHUNT_LO: R_SHUNT.3, U2.2
SW_BUCK: L1.1, U3.1
USB_CC1: J4.A12, R10.1
USB_CC2: J4.B12, R11.1
USB_DM: J4.A5, U1.14
USB_DP: J4.B5, U1.15
VBUS_FILT: C9.1, R5.2, U2.9

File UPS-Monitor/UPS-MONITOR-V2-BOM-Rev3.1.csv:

Qty,Designator,Value,Description,Package,Notes
1,U1,ESP32-C3-MINI-1-N4,WiFi/BLE MCU module,Module,Integrated PCB antenna; no external antenna required
1,U2,INA228AIDGST,85V 20-bit power monitor,MSOP-10,I2C addr 0x40; reset_on_boot: false to preserve energy accumulator
1,U3,AP63203WU-7,2A synchronous buck converter,SOT-23-6,13.3V→3.3V; Vout set by R6/R7
1,R_SHUNT,WSLT2512R0100FEA,10mΩ 1% Kelvin shunt,WSK2512 (6332),Vishay TRUE 4-terminal; 1W rated
2,"R1, R2",4.7k 1% 0402,I2C SDA/SCL pullups,0402,
1,R3,10k 5% 0402,INA228 A0/A1 address pulldown,0402,Both address pins to GND → I2C addr 0x40
1,R4,100R 5% 0402,LED current limit,0402,
1,R5,10R 5% 0402,INA228 VBUS series filter,0402,LOAD_OUT → R5 → U2 pin9 VBUS. RC pole with C9 at 160kHz
1,R6,210k 1% 0402,Buck FB divider top,0402,Sets 3.3V output with R7
1,R7,68k 1% 0402,Buck FB divider bottom,0402,
1,R8,10k 5% 0402,ESP32 EN pullup,0402,
1,R9,4.7k 5% 0402,DS18B20 data pullup,0402,Required for OneWire
2,"R10, R11",5.1k 5% 0402,USB-C CC1/CC2,0402,Device identification resistors
1,C1,100uF 25V,Input bulk cap,Electrolytic 6.3x5.4mm,Low ESR preferred
1,C2,10uF 25V X5R,LOAD_OUT filter,0805 MLCC,
1,C3,22uF 10V X5R,3.3V output cap,0805 MLCC,
5,"C4, C5, C6, C7, C9",100nF 10V+ X7R,Bypass / filter caps,0402 MLCC,C4=3.3V; C5/C6=ESP32; C7=buck HF; C9=INA228 VBUS filter (with R5)
1,C8,1uF 10V X5R,ESP32 EN RC cap,0402 MLCC,τ=10ms with R8 10kΩ. MUST be 1µF — not 100nF
1,L1,4.7uH 2.6A IHLP-5050FD,Buck inductor — superior DCR vs EZ variant,Vishay IHLP5050FDER4R7M01,Low DCR 8.7mΩ; same footprint as EZ. Backup: SHOU HAN CYA0630 C5189748 (verify land pattern before ordering)
1,TVS1,SMAJ15CA,15V bidirectional TVS,SMA,Input transient protection
1,J1,"Phoenix Contact SPT-SMD 1,5/2-V-5,0 R24",2P SMD push-in terminal — 5.0mm pitch,Phoenix Contact 1824307,12V battery input | HAND PLACEMENT - PCBWay
1,J2,"Phoenix Contact SPT-SMD 1,5/2-V-5,0 R24",2P SMD push-in terminal — 5.0mm pitch,Phoenix Contact 1824307,12V load output | HAND PLACEMENT - PCBWay
1,J3,PinHeader 1x03 2.54mm,DS18B20 header,Through-hole 2.54mm,VCC / DATA / GND | HAND PLACEMENT - PCBWay
1,J4,USB4110-GF-A,USB-C edge-mount receptacle (16-pin USB 2.0),GCT USB4110-GF-A,WARNING: disconnect 12V before connecting USB — VBUS tied to LOAD_OUT | HAND PLACEMENT - PCBWay
1,LED1,Blue 0402,Status LED,0402,
2,"SW1, SW2",Omron B3S-1000,BOOT / RESET tactile switch,SMD B3S-1000,SW1=BOOT (GPIO9); SW2=RESET (EN) | HAND PLACEMENT - PCBWay

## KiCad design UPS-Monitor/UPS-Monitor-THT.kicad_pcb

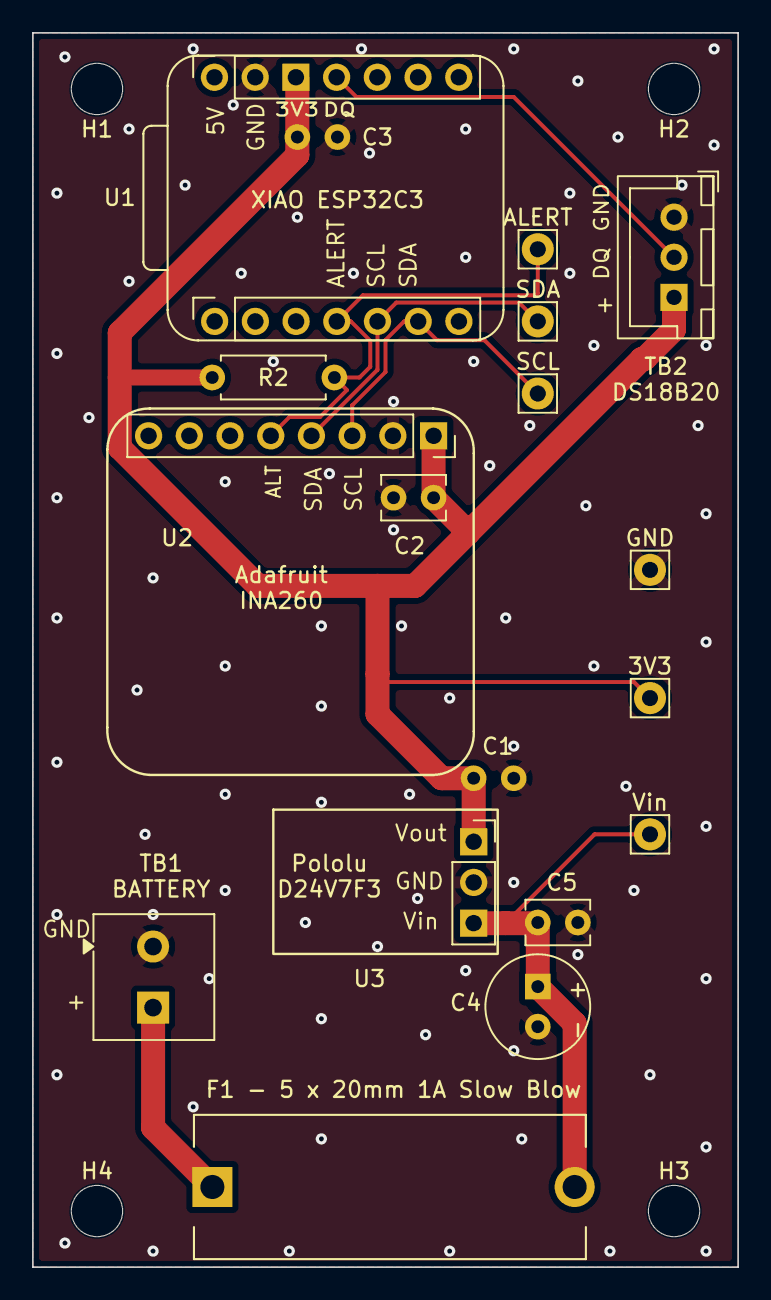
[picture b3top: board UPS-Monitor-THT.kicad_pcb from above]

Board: 2 copper layers, 44.0 x 77.0 mm, 22 parts (0 on the bottom side), 8 nets.

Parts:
3V3: TestPoint_THTPad_2.0x2.0mm_Drill1.0mm
ALERT: TestPoint_THTPad_2.0x2.0mm_Drill1.0mm
C1: C_Disc_D5.0mm_W2.5mm_P2.50mm
C2, C3, C5: 0.1uF cer 50V; C_Disc_D3.8mm_W2.6mm_P2.50mm
C4: C_Radial_D6.3mm_H11.0mm_P2.50mm
F1: 1A SB Wurth 696108003002; Wuerth_696108003002
GND: TestPoint_THTPad_2.0x2.0mm_Drill1.0mm
H1, H2, H3, H4: M3; MountingHole_3.2mm_M3
R2: R_Axial_DIN0207_L6.3mm_D2.5mm_P7.62mm_Horizontal
SCL: TestPoint_THTPad_2.0x2.0mm_Drill1.0mm
SDA: TestPoint_THTPad_2.0x2.0mm_Drill1.0mm
TB1: TerminalBlock_Phoenix_MKDS-1-2-3.81_1x02_P3.81mm_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; TerminalBlock_Phoenix_MKDS-1-2-3.81_1x02_P3.81mm_Horizontal
TB2: JST_XH_B3B-XH-A_1x03_P2.50mm_Vertical
U1: Xiao ESP32C3; XIAO ESP32C3
U2: INA260/INA228; PinSocket_1x08_P2.54mm_Vertical
U3: Pololu D24V7F3; PinSocket_1x03_P2.54mm_Vertical
Vin: TestPoint_THTPad_2.0x2.0mm_Drill1.0mm

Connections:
+3V3: 3V3.1, C1.1, C2.2, C3.2, R2.2, TB2.3, U1.3V3, U2.1, U3.1
BATT_RAW: F1.1, TB1.2
GND: C1.2, C2.1, C3.1, C4.2, C5.1, GND.1, TB1.1, TB2.1, U1.GND, U2.2, U3.2
GPIO3_ALERT: ALERT.1, R2.1, U1.GPIO3, U2.5
GPIO10_DQ: TB2.2, U1.GPIO10
SCL: SCL.1, U1.SCL, U2.3
SDA: SDA.1, U1.SDA, U2.4
VIN: C4.1, C5.2, F1.2, U3.3, Vin.1

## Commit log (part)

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2026-03-06 Add system architecture diagram
    Added system architecture diagram to README.
2026-03-06 Fix image filename in README.md
    Corrected the image filename for system architecture.
2026-03-06 Update README with system architecture image
    Added system architecture image to README and removed detailed diagram.
2026-03-06 Remove system architecture image from README
    Removed system architecture image from README.
2026-03-06 Include system architecture diagram
    Add system architecture image to README
2026-03-09 Correct link format for Shelly Plus Uni manual
    Fixed a broken link for the Shelly Plus Uni manual.
2026-03-09 Fix link formatting for Shelly Plus Uni manual
2026-03-10 Revise README for clarity and updated metrics
    Updated performance metrics and specifications for clarity. Revised context and notes for better understanding.
2026-03-10 Replace terminal block module with Wago lever nuts
2026-03-10 Add README for Home Assistant UPS Automation
    Added detailed documentation for Home Assistant UPS automation, including hardware context, sensor pipeline, automation architecture, temperature automations, and reliability notes.
2026-03-15 Fix image file name in README.md
2026-03-15 Fix image filename in README.md
2026-03-16 Fix image path for system architecture diagram
    Updated image reference for system architecture in README.
2026-03-16 Fix image filename in README
    Updated image filename for system architecture diagram.
2026-03-28 Add assembly pictures to README
2026-03-29 Modify battery telemetry range and shutdown timing
    Updated battery voltage telemetry range and adjusted shutdown timing details.
2026-03-29 Create Test_D3_March_2026_Voltage
2026-03-29 Document UPS performance and runtime limitations
    Added performance summary and discharge characteristics for UPS runtime.
2026-03-29 Fix typo in README for report location
2026-03-29 Fix link formatting in README.md
2026-03-30 Revise UPS Validation Report for accuracy and clarity
    Updated UPS performance validation report with refined metrics and conclusions.
2026-03-30 Update status badge and mark documentation as complete
2026-03-30 Add UPS Validation Report link to README
2026-04-06 Add inaugural commissioning report for DIY LiFePO4 UPS
    This inaugural report documents the commissioning of the DIY LiFePO4 UPS, including controlled discharge tests and monitoring results.
2026-04-06 Fix image paths in UPS_Report_2026-04-05.md
    Updated image paths in the UPS report to use relative paths from the assets directory.
2026-04-06 Update image paths in UPS report
2026-04-07 chore: install pre-commit and update documentation/reports
2026-04-12 Updated and corrected component parts - terminal block, USB-C
2026-04-12 Add Operational Specifications
2026-04-13 PCB Screen Shot
2026-04-13 Firmware Rev0
2026-04-13 improved doc format
2026-04-13 Update Firmware README with Markdown formatting
2026-05-01 Data Sheets
2026-05-06 Added and validated new ESP32-C3, Adafruit INA260, Pololu Buck Converter
2026-05-06 Full Commissioning validation with new monitoring system; ESP32-C3, Adafruit INA260, Pololu Buck Converter
2026-05-17 May Discharge and commissioning test
2026-05-19 Corrected
2026-05-24 Added deep sleep mode to monitor

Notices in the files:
README.md:
License: MIT
